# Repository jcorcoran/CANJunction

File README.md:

# CANJunction
PCB project to aid CAN wire distribution

This PCB can be ordered from any fab house using the files in the [gerbers](gerbers) directory of this repository, including [oshpark](https://oshpark.com/shared_projects/lZ9DFcMB).  

Apply a piece of electrical or kaptop tape to the bottom of the PCB if it is going to be mounted diretly to a conductive surface.

## Parts:

The PCB uses push to connect terminal blocks. The part footprint is designed to allow any style connector that's typically found in this spacing.

We tend to use the Combicon PTSA family of [pheonix contacts](https://www.digikey.com/short/zdrh8825) ordering yellow and green pairs and then manually assemble them in alternating colors. Works with stripped wire (no connector/ferrule required) 16-24 awg.  
These connectors are also typically stocked at mouser. They can also be had from ebay/[aliexpress](https://www.aliexpress.com/item/32880938989.html). We haven't had problems with the off-brand ones, but YMMV.

## CAD

A step model of the PCB is [here](cad/)

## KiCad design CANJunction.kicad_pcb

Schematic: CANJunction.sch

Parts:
H1: MountingHole; mounting_holes
J1, J3: Screw_Terminal_01x02; TerminalBlock_Spring_2Pos_3.5mm
J2: Screw_Terminal_01x06; TerminalBlock_Spring_6Pos_3.5mm

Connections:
unnamed: J1.1, J2.1, J2.3, J2.5, J3.1
unnamed: J1.2, J2.2, J2.4, J2.6, J3.2

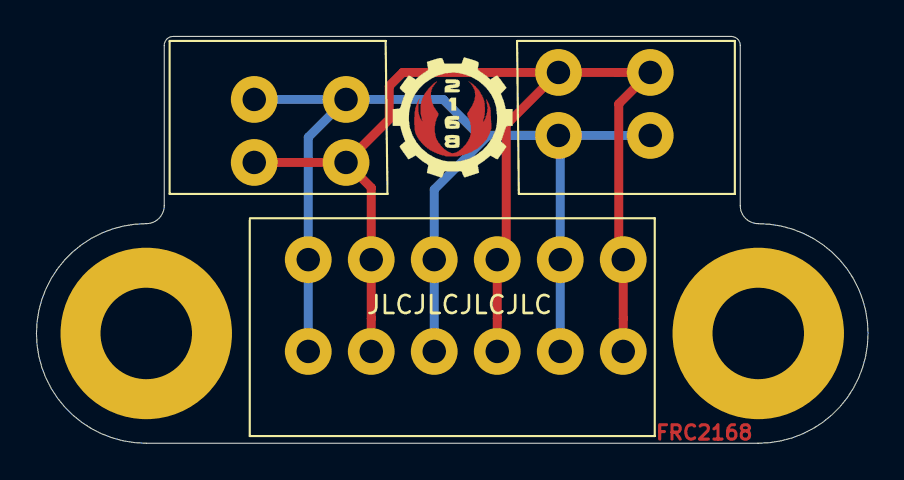
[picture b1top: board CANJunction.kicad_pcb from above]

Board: 2 copper layers, 46.2 x 22.6 mm, 6 parts (0 on the bottom side), 2 nets.

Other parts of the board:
Wings: LOGO; gear_small_wings-f.mask
Wings#2: LOGO; gear_small_wings-cu

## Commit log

2020-01-15 add all files
2021-08-03 Update README.md
    add bom info
2021-08-03 Create LICENSE
2021-08-03 Update README.md
    typo
2021-12-03 cleanup gerber organization
2021-12-03 add gitignore
2021-12-03 add 3d models and step update gerbers w/ edge cuts in mounting 'via' re-export gerbers
2021-12-03 saves
2021-12-03 remove tmp files from being tracked
2021-12-09 update layout mod hole to fit 3/16” rivet or “10 bolt
2021-12-09 in case I forgot to re-plot these...
2021-12-10 add direction to fab on where to place order number
2021-12-10 save project
2021-12-10 re-export gerbers to remove old copies of layers (e.g. drls)
